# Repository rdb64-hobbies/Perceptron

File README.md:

# Perceptron

This repository contains the build guide, PCB designs, circuit schematics, PCB manufacturing files (Gerbers), bill of materials (BoM), and 3D printable frame designs, everything you need to build your own Perceptron, just like the one described in my [video tutorial](https://www.youtube.com/watch?v=PSqP73T0g_M). It was inspired by this [video tutorial](https://www.youtube.com/watch?v=l-9ALe3U-Fg) by Welch Labs. I hope you'll check out both videos.

This little device is fun to build, and it provides a wonderful hands-on illustration of how neural networks are trained and how they work. It was the Welch Labs video that inspired me to do this, but dreading the prospect of all that point-to-point wire soldering (as in the Welch Labs version), I decided to make a PCB version. With the PCBs, it's really easy to build, and you can use it to teach someone about neural networks. So I hope you'll go ahead and build one.

Go right to the [build guide](BUILDING.md) and get started.

If you want to skip this build guide and just jump right in with the schematics, the PCB Gerbers, the BoM, and the 3D-print files, then here they are:

- Schematics:
  - [Input board](assets/schematic_input.pdf)
  - [Adder board](assets/schematic_adder.pdf)
- PCB Gerbers:
  - [Input board](PCBs/PerceptronInputGerbers.zip)
  - [Adder board](PCBs/PerceptronAdderGerbers.zip)
- BoM: [csv file](BoM.csv), [pdf file](assets/bom.pdf)
- 3D-print files: [Frames directory](Frames/)

## PCBs

The PCBs were designed using KiCad (https://www.kicad.org/), and you'll find the source files in the `PCBs` directory. There are two PCBs in two KiCad project directories:

- **PerceptronInput** - Input board with toggle switches and bi-color LEDs
- **PerceptronAdder** - Adder board with potentiometers for signal processing

If you just want the Gerber files to order from a PCB manufacturer, you can find them also in the `PCBs` directory. Each one is in its own zip archive file.

## 3D printable frames and knobs

The frames and knobs were designed using Fusion 360 (https://www.autodesk.com/products/fusion-360/), and you'll find everything in the `Frames` directory. The complete Fusion 360 archive file is there along with all of the 3D printable 3mf files. The 3mf files come directly from Fusion 360, so they contain only model information, no printer or slicer settings.

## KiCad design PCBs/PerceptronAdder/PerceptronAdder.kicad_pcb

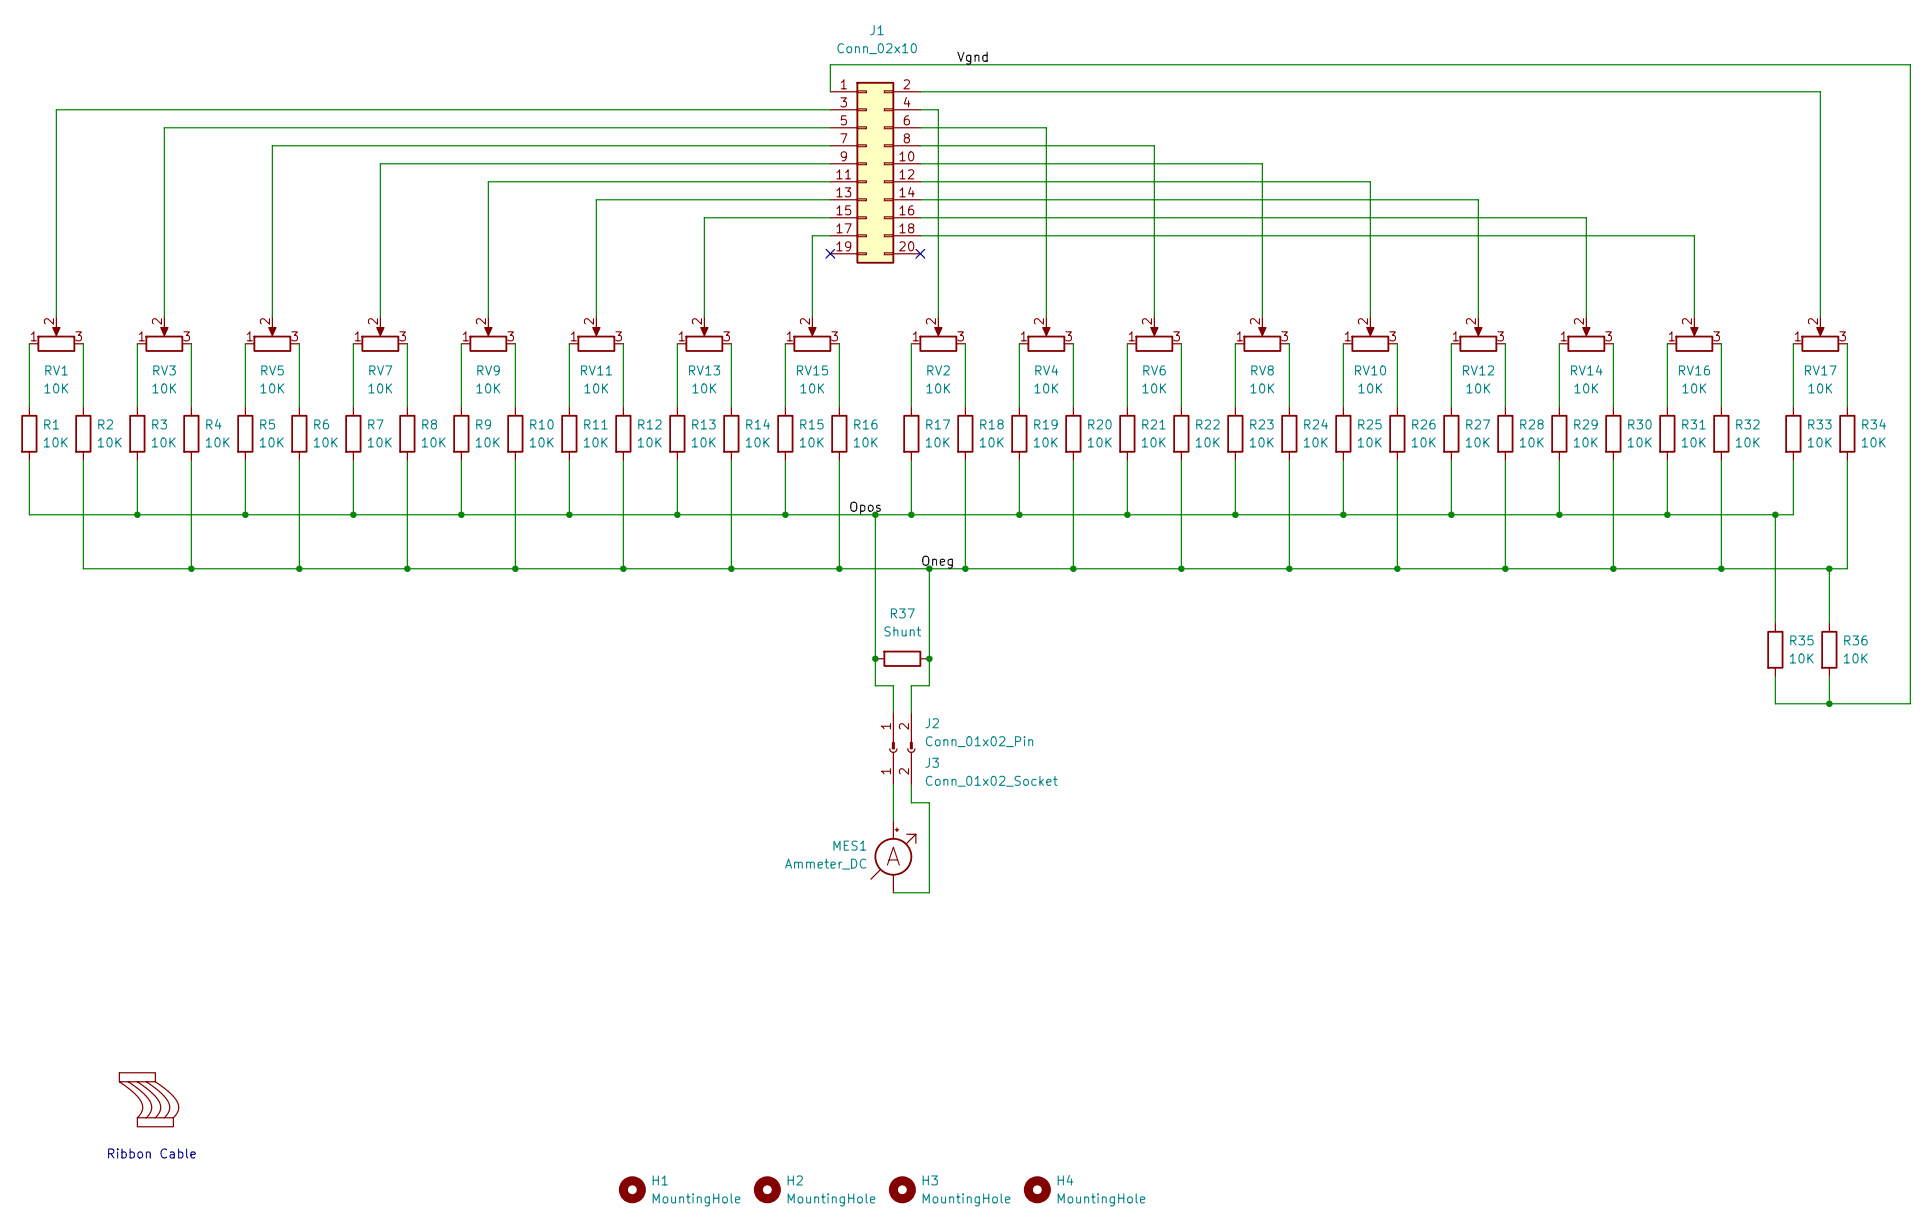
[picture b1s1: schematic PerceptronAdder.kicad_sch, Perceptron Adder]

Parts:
H1, H2, H3, H4: MountingHole; MountingHole_3.2mm_M3_Pad
J1: Conn_02x10; PinHeader_2x10_P2.54mm_Vertical
J2: Conn_01x02_Pin; Molex_KK-254_1x02_P2.54mm_Vertical
J3: Conn_01x02_Socket
MES1: Ammeter_DC
R1, R2, R3, R4, R5, R6, R7, R8, R9, R10, R11, R12, R13, R14, R15, R16, R17, R18, R19, R20, R21, R22, R23, R24, R25, R26, R27, R28, R29, R30, R31, R32, R33, R34, R35, R36: 10K; R_Axial_DIN0207_L6.3mm_D2.5mm_P7.62mm_Horizontal
R37: Shunt; R_Axial_DIN0207_L6.3mm_D2.5mm_P7.62mm_Horizontal
RC1: 20P
RV1, RV2, RV3, RV4, RV5, RV6, RV7, RV8, RV9, RV10, RV11, RV12, RV13, RV14, RV15, RV16, RV17: 10K; Potentiometer_Bourns_PTV09A-1_Single_Vertical

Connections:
/Oneg: J2.2, R2.2, R4.2, R6.2, R8.2, R10.2, R12.2, R14.2, R16.2, R18.2, R20.2, R22.2, R24.2, R26.2, R28.2, R30.2, R32.2, R34.2, R36.1, R37.1
/Opos: J2.1, R1.2, R3.2, R5.2, R7.2, R9.2, R11.2, R13.2, R15.2, R17.2, R19.2, R21.2, R23.2, R25.2, R27.2, R29.2, R31.2, R33.2, R35.1, R37.2
/Vgnd: J1.1, R35.2, R36.2
unnamed: J1.2, RV17.2
unnamed: J1.3, RV1.2
unnamed: J1.4, RV2.2
unnamed: J1.5, RV3.2
unnamed: J1.6, RV4.2
unnamed: J1.7, RV5.2
unnamed: J1.8, RV6.2
unnamed: J1.9, RV7.2
unnamed: J1.10, RV8.2
unnamed: J1.11, RV9.2
unnamed: J1.12, RV10.2
unnamed: J1.13, RV11.2
unnamed: J1.14, RV12.2
unnamed: J1.15, RV13.2
unnamed: J1.16, RV14.2
unnamed: J1.17, RV15.2
unnamed: J1.18, RV16.2
unnamed: J3.1, MES1.2 (+)
unnamed: J3.2, MES1.1 (-)
unnamed: R1.1, RV1.1
unnamed: R2.1, RV1.3
unnamed: R3.1, RV3.1
unnamed: R4.1, RV3.3
unnamed: R5.1, RV5.1
unnamed: R6.1, RV5.3
unnamed: R7.1, RV7.1
unnamed: R8.1, RV7.3
unnamed: R9.1, RV9.1
unnamed: R10.1, RV9.3
unnamed: R11.1, RV11.1
unnamed: R12.1, RV11.3
unnamed: R13.1, RV13.1
unnamed: R14.1, RV13.3
unnamed: R15.1, RV15.1
unnamed: R16.1, RV15.3
unnamed: R17.1, RV2.1
unnamed: R18.1, RV2.3
unnamed: R19.1, RV4.1
unnamed: R20.1, RV4.3
unnamed: R21.1, RV6.1
unnamed: R22.1, RV6.3
unnamed: R23.1, RV8.1
unnamed: R24.1, RV8.3
unnamed: R25.1, RV10.1
unnamed: R26.1, RV10.3
unnamed: R27.1, RV12.1
unnamed: R28.1, RV12.3
unnamed: R29.1, RV14.1
unnamed: R30.1, RV14.3
unnamed: R31.1, RV16.1
unnamed: R32.1, RV16.3
unnamed: R33.1, RV17.1
unnamed: R34.1, RV17.3

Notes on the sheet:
Ribbon Cable

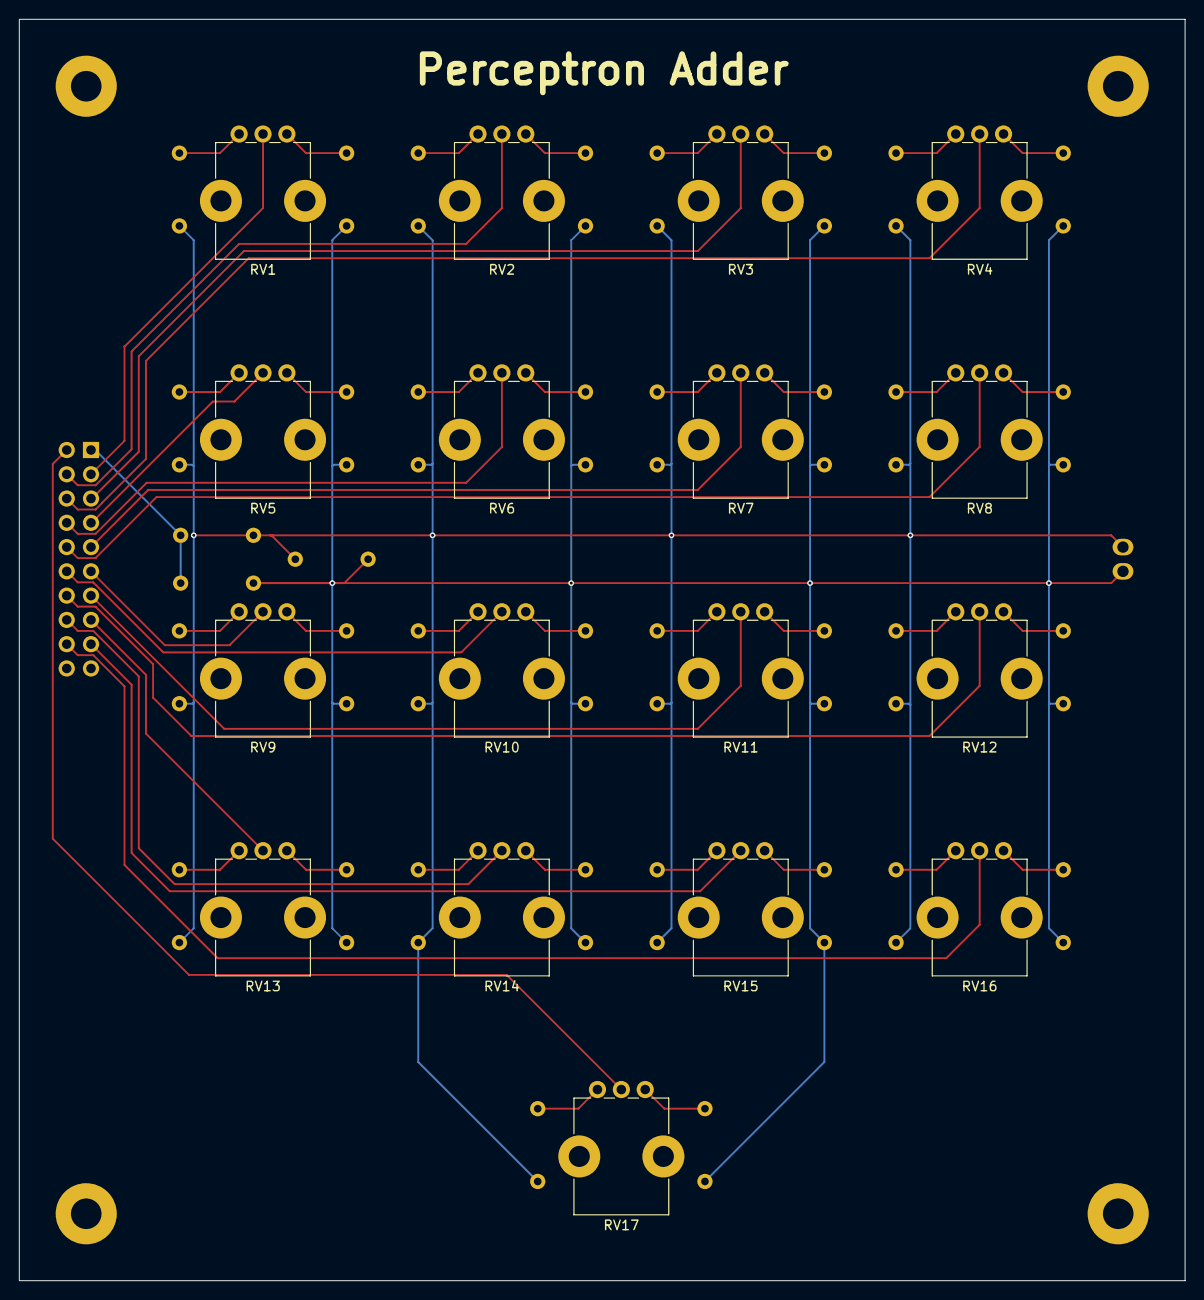
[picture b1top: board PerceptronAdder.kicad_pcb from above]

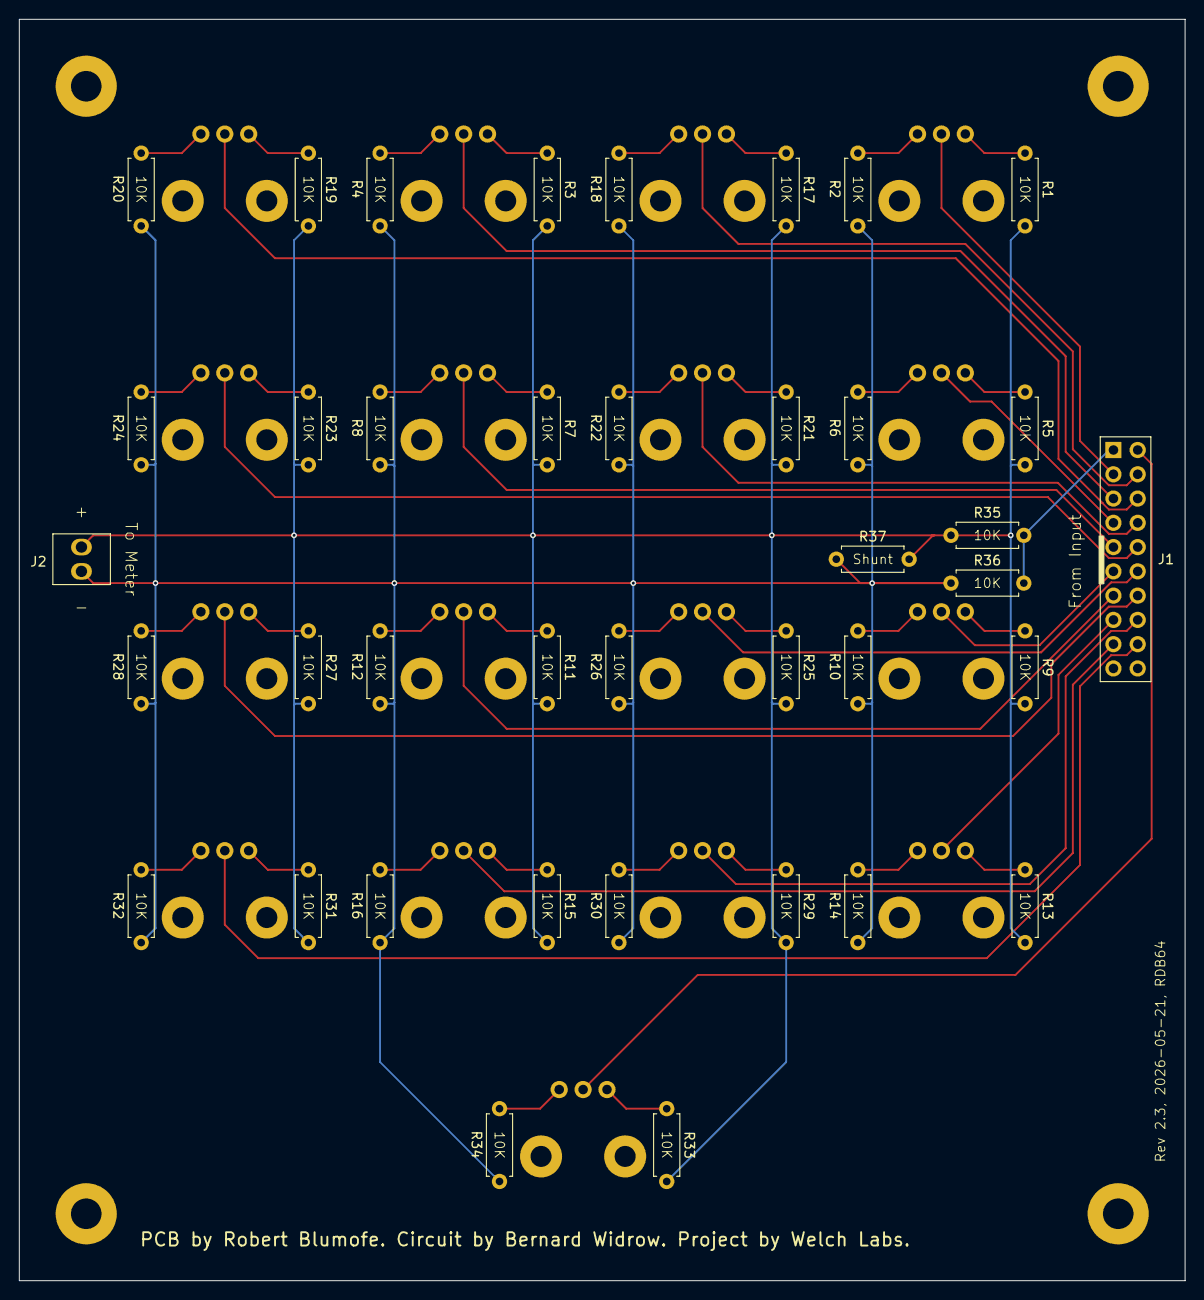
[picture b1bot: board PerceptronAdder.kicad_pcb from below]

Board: 2 copper layers, 122.0 x 132.0 mm, 60 parts (39 on the bottom side), 54 nets.

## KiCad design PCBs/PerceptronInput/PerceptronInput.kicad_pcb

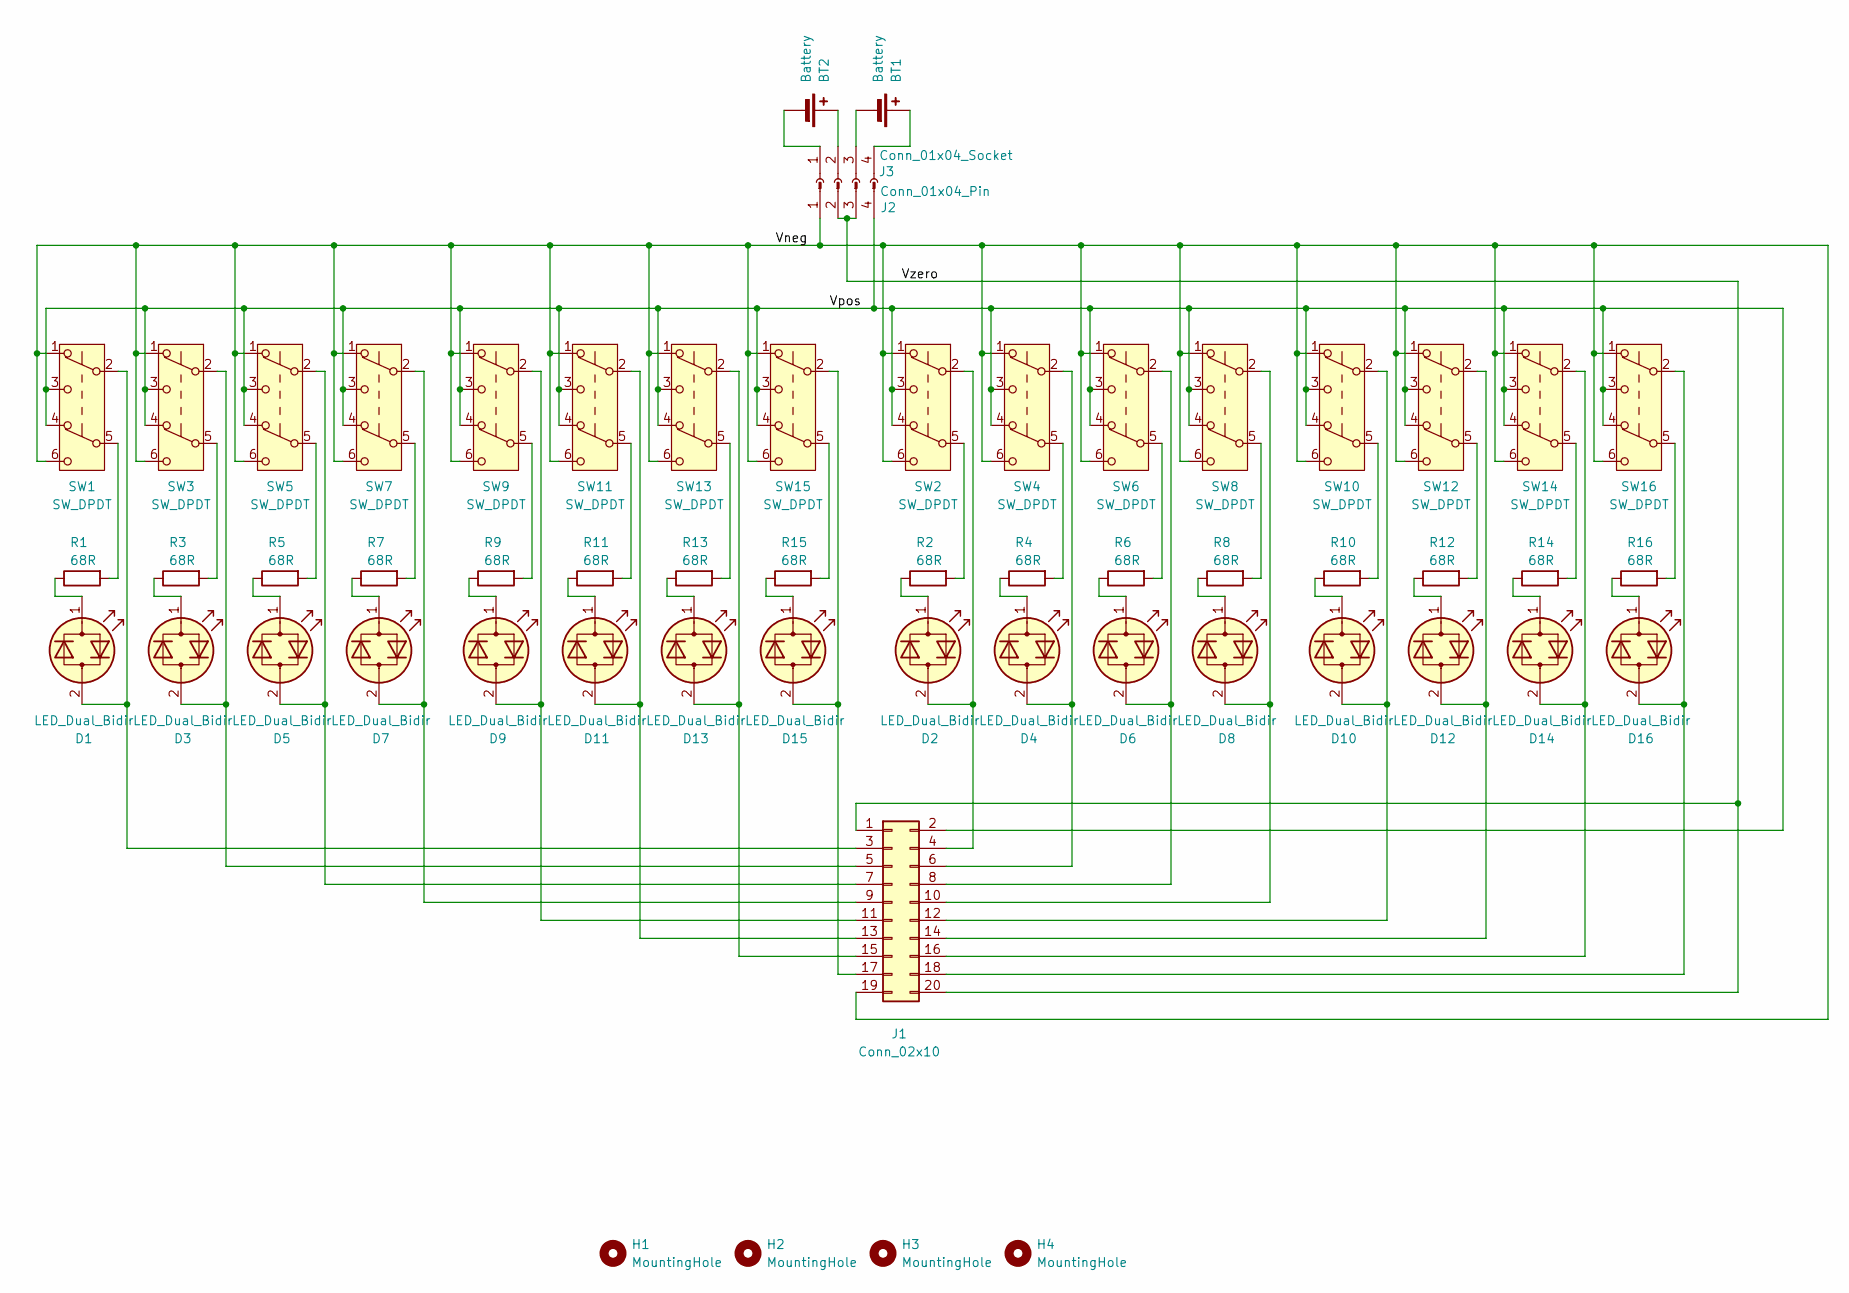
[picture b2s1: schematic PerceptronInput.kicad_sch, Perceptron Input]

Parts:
BT1, BT2: Battery
D1, D2, D3, D4, D5, D6, D7, D8, D9, D10, D11, D12, D13, D14, D15, D16: LED_Dual_Bidir; LED_D5.0mm_Bicolor_Bidirection
H1, H2, H3, H4: MountingHole; MountingHole_3.2mm_M3_Pad
J1: Conn_02x10; PinHeader_2x10_P2.54mm_Vertical
J2: Conn_01x04_Pin; Molex_KK-254_1x04_P2.54mm_Vertical
J3: Conn_01x04_Socket
R1, R2, R3, R4, R5, R6, R7, R8, R9, R10, R11, R12, R13, R14, R15, R16: 68R; R_Axial_DIN0207_L6.3mm_D2.5mm_P7.62mm_Horizontal
SW1, SW2, SW3, SW4, SW5, SW6, SW7, SW8, SW9, SW10, SW11, SW12, SW13, SW14, SW15, SW16: SW_DPDT; SW_Toggle_E-Switch_100A_DPDT_M2

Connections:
/Vneg: J1.19, J2.1, SW1.1 (A), SW1.6 (C), SW2.1 (A), SW2.6 (C), SW3.1 (A), SW3.6 (C), SW4.1 (A), SW4.6 (C), SW5.1 (A), SW5.6 (C), SW6.1 (A), SW6.6 (C), SW7.1 (A), SW7.6 (C), SW8.1 (A), SW8.6 (C), SW9.1 (A), SW9.6 (C), SW10.1 (A), SW10.6 (C), SW11.1 (A), SW11.6 (C), SW12.1 (A), SW12.6 (C), SW13.1 (A), SW13.6 (C), SW14.1 (A), SW14.6 (C), SW15.1 (A), SW15.6 (C), SW16.1 (A), SW16.6 (C)
/Vpos: J1.2, J2.4, SW1.3 (C), SW1.4 (A), SW2.3 (C), SW2.4 (A), SW3.3 (C), SW3.4 (A), SW4.3 (C), SW4.4 (A), SW5.3 (C), SW5.4 (A), SW6.3 (C), SW6.4 (A), SW7.3 (C), SW7.4 (A), SW8.3 (C), SW8.4 (A), SW9.3 (C), SW9.4 (A), SW10.3 (C), SW10.4 (A), SW11.3 (C), SW11.4 (A), SW12.3 (C), SW12.4 (A), SW13.3 (C), SW13.4 (A), SW14.3 (C), SW14.4 (A), SW15.3 (C), SW15.4 (A), SW16.3 (C), SW16.4 (A)
/Vzero: J1.1, J1.20, J2.2, J2.3
unnamed: BT1.1 (+), J3.4
unnamed: BT1.2 (-), J3.3
unnamed: BT2.1 (+), J3.2
unnamed: BT2.2 (-), J3.1
unnamed: D1.2 (AK), J1.3, SW1.2 (B)
unnamed: D1.1 (KA), R1.1
unnamed: D2.2 (AK), J1.4, SW2.2 (B)
unnamed: D2.1 (KA), R2.1
unnamed: D3.2 (AK), J1.5, SW3.2 (B)
unnamed: D3.1 (KA), R3.1
unnamed: D4.2 (AK), J1.6, SW4.2 (B)
unnamed: D4.1 (KA), R4.1
unnamed: D5.2 (AK), J1.7, SW5.2 (B)
unnamed: D5.1 (KA), R5.1
unnamed: D6.2 (AK), J1.8, SW6.2 (B)
unnamed: D6.1 (KA), R6.1
unnamed: D7.2 (AK), J1.9, SW7.2 (B)
unnamed: D7.1 (KA), R7.1
unnamed: D8.2 (AK), J1.10, SW8.2 (B)
unnamed: D8.1 (KA), R8.1
unnamed: D9.2 (AK), J1.11, SW9.2 (B)
unnamed: D9.1 (KA), R9.1
unnamed: D10.2 (AK), J1.12, SW10.2 (B)
unnamed: D10.1 (KA), R10.1
unnamed: D11.2 (AK), J1.13, SW11.2 (B)
unnamed: D11.1 (KA), R11.1
unnamed: D12.2 (AK), J1.14, SW12.2 (B)
unnamed: D12.1 (KA), R12.1
unnamed: D13.2 (AK), J1.15, SW13.2 (B)
unnamed: D13.1 (KA), R13.1
unnamed: D14.2 (AK), J1.16, SW14.2 (B)
unnamed: D14.1 (KA), R14.1
unnamed: D15.2 (AK), J1.17, SW15.2 (B)
unnamed: D15.1 (KA), R15.1
unnamed: D16.2 (AK), J1.18, SW16.2 (B)
unnamed: D16.1 (KA), R16.1
unnamed: R1.2, SW1.5 (B)
unnamed: R2.2, SW2.5 (B)
unnamed: R3.2, SW3.5 (B)
unnamed: R4.2, SW4.5 (B)
unnamed: R5.2, SW5.5 (B)
unnamed: R6.2, SW6.5 (B)
unnamed: R7.2, SW7.5 (B)
unnamed: R8.2, SW8.5 (B)
unnamed: R9.2, SW9.5 (B)
unnamed: R10.2, SW10.5 (B)
unnamed: R11.2, SW11.5 (B)
unnamed: R12.2, SW12.5 (B)
unnamed: R13.2, SW13.5 (B)
unnamed: R14.2, SW14.5 (B)
unnamed: R15.2, SW15.5 (B)
unnamed: R16.2, SW16.5 (B)

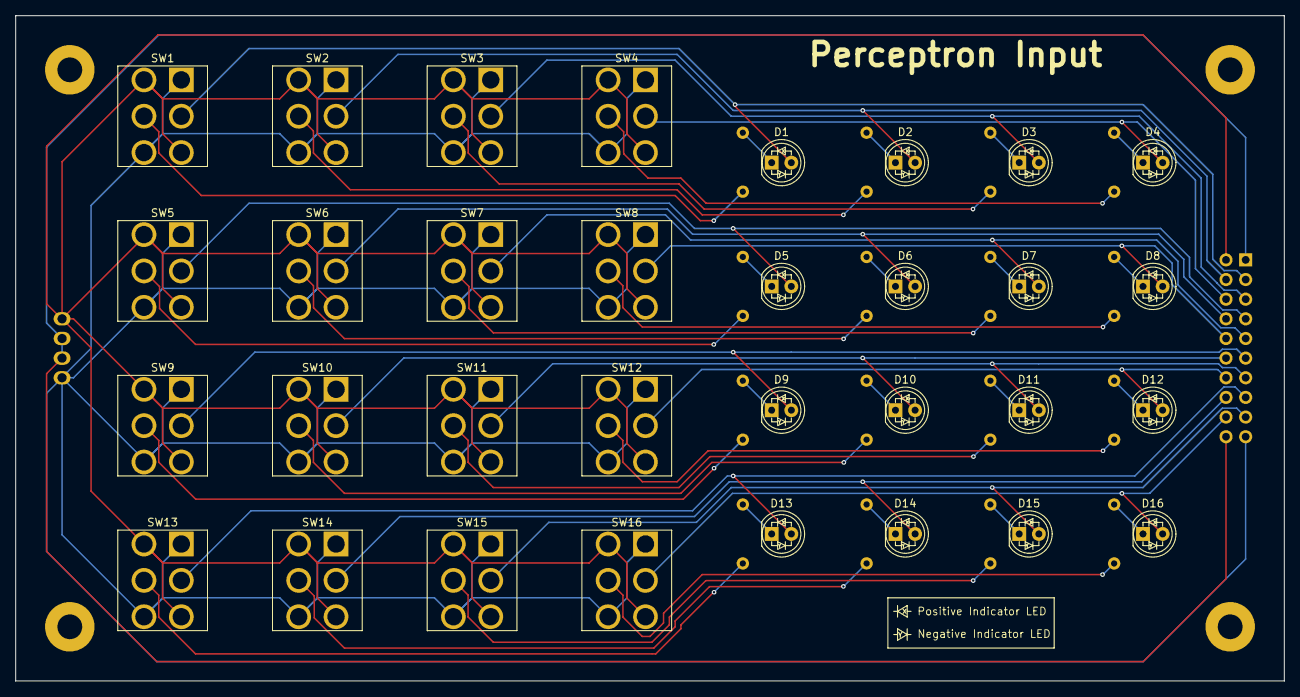
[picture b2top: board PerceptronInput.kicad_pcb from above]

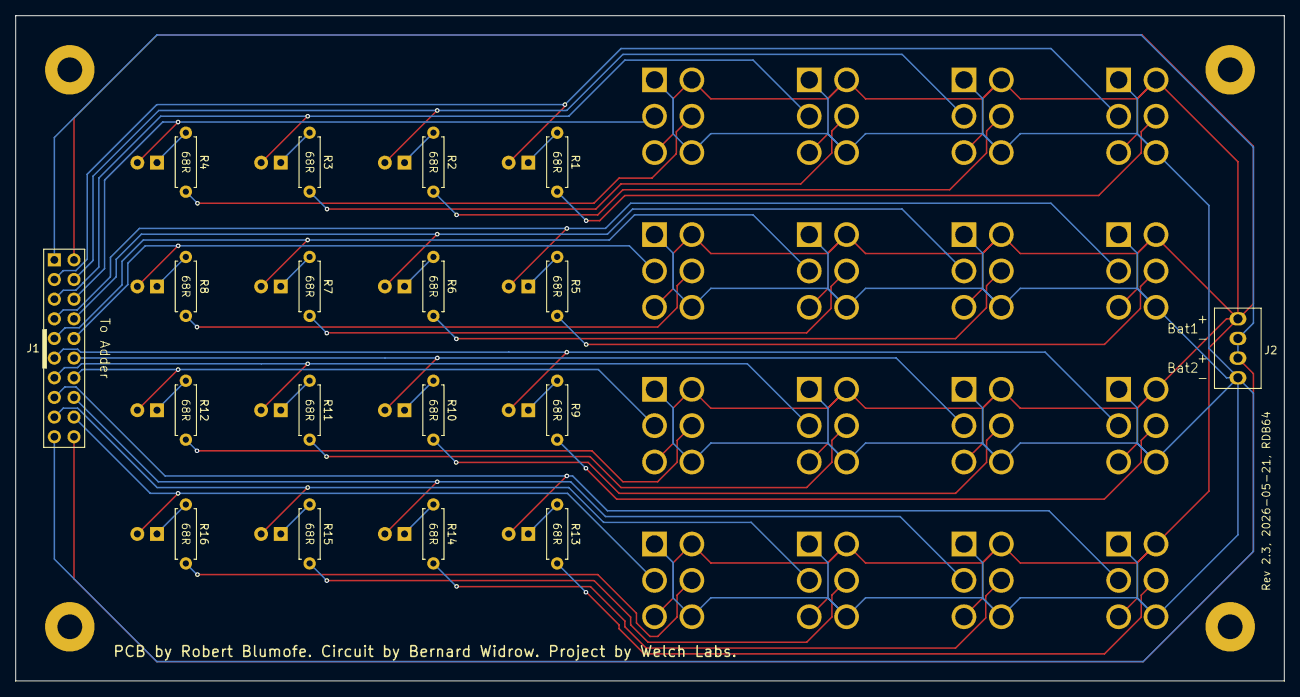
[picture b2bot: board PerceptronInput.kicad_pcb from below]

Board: 2 copper layers, 164.0 x 86.0 mm, 54 parts (18 on the bottom side), 51 nets.

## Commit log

2026-02-18 Add README
2026-02-18 Add MIT License
2026-02-18 Add Gerber files for PCB manufacturing
2026-02-18 Add bill of materials (BoM) files
2026-02-18 Get the right BoM fields
2026-02-18 Remove PerceptronAdder.csv
2026-02-18 Remove PerceptronInput.csv
2026-02-18 Edit BoM by hand
2026-02-18 Add build guide with images
2026-02-19 Minor edits
2026-02-20 Remove built.png
2026-02-20 Remove built_noframe.png
2026-02-20 Change images to jpgs.
2026-02-20 Start writing the PCB part of the build guide.
2026-02-20 Get rid of jlc silkscreen.
2026-02-20 Complete PCBs section
2026-02-20 Complete guide for jlcpcb with images.
2026-02-20 Fix jlcpcb images
2026-02-20 Minor edits on build guide and jlcpcb guide.
2026-02-20 Provide a little more background.
2026-02-20 Minor edit.
2026-02-21 Add in and explain the BoM.
2026-02-21 Explain the battery holders and crimping.
2026-02-21 Fill in outline.
2026-02-21 Put in schematics.
2026-02-21 Write Meter section.
2026-03-01 Add information about other components.
2026-03-02 First draft of soldering section without the photos.
2026-03-02 Write the soldering section.
2026-03-03 Add photos for rear side soldering.
2026-03-03 Add photos for front side soldering.
2026-03-05 Get the right meters in the BoM, add a photo, and update that section to reflect these meters.
2026-03-08 Update images and add a skip-ahead to the intro section.
2026-03-08 Write section 4.
2026-03-09 Write section for optional components.
2026-03-09 Add a bit more sub-sectioning.
2026-03-09 Add Frames directory and contents
2026-03-09 Start writing the Build Frames section.
2026-03-09 Write the Frames section.
2026-03-09 Minor edits across the whole thing.
2026-03-09 Minor edits plus complete the README.
2026-03-10 Explain self tapping the screw holes.
2026-03-10 Note that PCB photos are earlier revision.
2026-03-11 Minor update to PCB silkscreen.
2026-03-11 Update the section on obtaining the PCBs.
2026-03-11 Add info about the build time option.
2026-03-13 Create simplified instructions for PCBWay.
2026-03-20 Put in link to video.
2026-03-21 Add some info about the 3D print files.
2026-04-05 Add knob.3mf to Frames
2026-04-05 Remove knobs from BoM and add alternate link for ribbon cable.
2026-04-05 Add info about buying or printing knobs.
2026-04-05 Add info about the knobs.
2026-04-05 Provide photos with the 3D printed knobs.
2026-05-21 Added resistor values to silkscreen.
2026-06-06 Support flat, D-shaped knobs.
